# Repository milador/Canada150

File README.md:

# canada150
A PCB to celebrate Canada's 150th birthday

Part List:

    Coin Cell Battery Holder - 20mm x 1 https://www.sparkfun.com/products/783

    Mini Speaker - PC Mount 12mm 2.048kHz x 1 https://www.sparkfun.com/products/7950

    AVR 8 Pin 20MHz 8K 4A/D - ATtiny85 x 1 https://www.sparkfun.com/products/9378

    SPDT Mini Power Switch x 1 https://www.sparkfun.com/products/102

    LED - Basic Red 5mm x 6 https://www.sparkfun.com/products/9590

    DIP Sockets Solder Tail - 8-Pin x 1 (Optional) https://www.sparkfun.com/products/7937

    Header - 2x3 (Male, 0.1") x 1 https://www.sparkfun.com/products/12807 http://www.digikey.com/product-detail/en/amphenol-fci/67997-206HLF/609-3234-ND/1878491

    100 Ohm 1/4W 5% CF MINI x 4 http://www.digikey.ca/product-detail/en/stackpole-electronics-inc/CFM14JT100R/S100QCT-ND/2617658

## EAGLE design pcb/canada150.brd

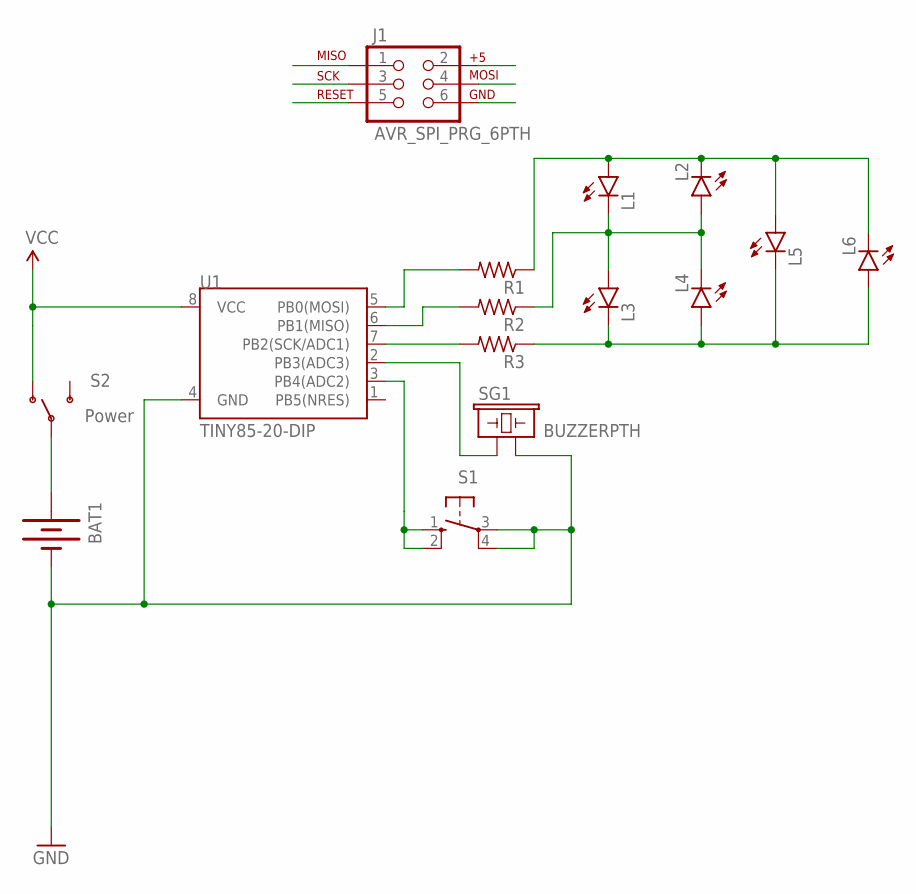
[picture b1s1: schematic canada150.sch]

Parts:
BAT1: BATTERY20PTH; BATTCOM_20MM_PTH
J1: AVR_SPI_PRG_6PTH; 2X3
L1, L2, L3, L4, L5, L6: LED5MM
R1, R2, R3: R-US_0204/7; 0204/7
S1: 10-XX; B3F-10XX
S2: Power; SWITCH-SPDT
SG1: BUZZERPTH; BUZZER-12MM
U1: TINY85-20-DIP; DIP08

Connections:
GND: BAT1.2 (-), J1.6, S1.3, S1.4 (P1), SG1.- (2), U1.4 (GND)
L12: L1.K (C), L2.A, L3.A, L4.K (C), R2.1
MISO: J1.1, R2.2, U1.6 (PB1(MISO))
MOSI: J1.4, R1.2, U1.5 (PB0(MOSI))
unnamed: BAT1.1 (+), S2.2
unnamed: L3.K (C), L4.A, L5.K (C), L6.A, R3.1
unnamed: S1.1 (S), S1.2 (S1), U1.3 (PB4(ADC2))
unnamed: SG1.+ (1), U1.2 (PB3(ADC3))
unnamed: L1.A, L2.K (C), L5.A, L6.K (C), R1.1
RST: J1.5
SCK: J1.3, R3.2, U1.7 (PB2(SCK/ADC1))
VCC: J1.2, S2.1 (O), U1.8 (VCC)

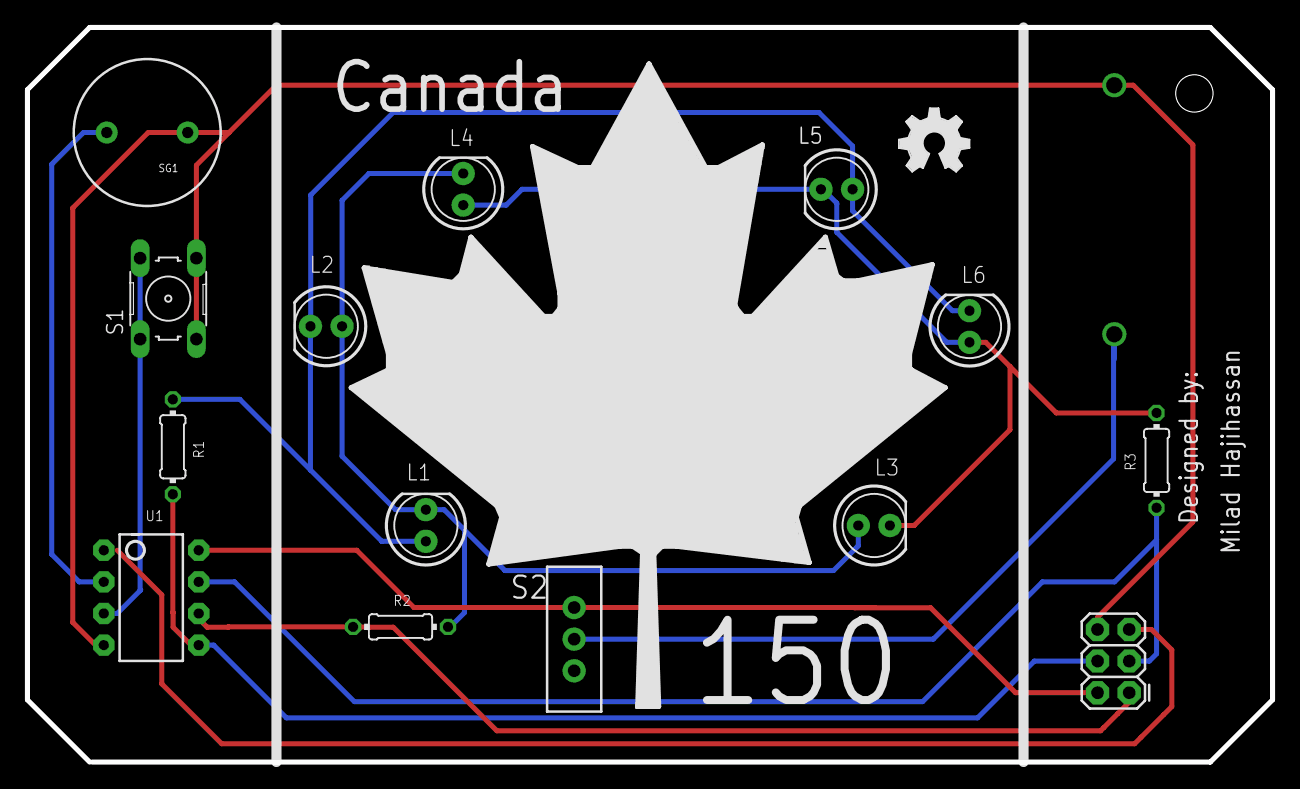
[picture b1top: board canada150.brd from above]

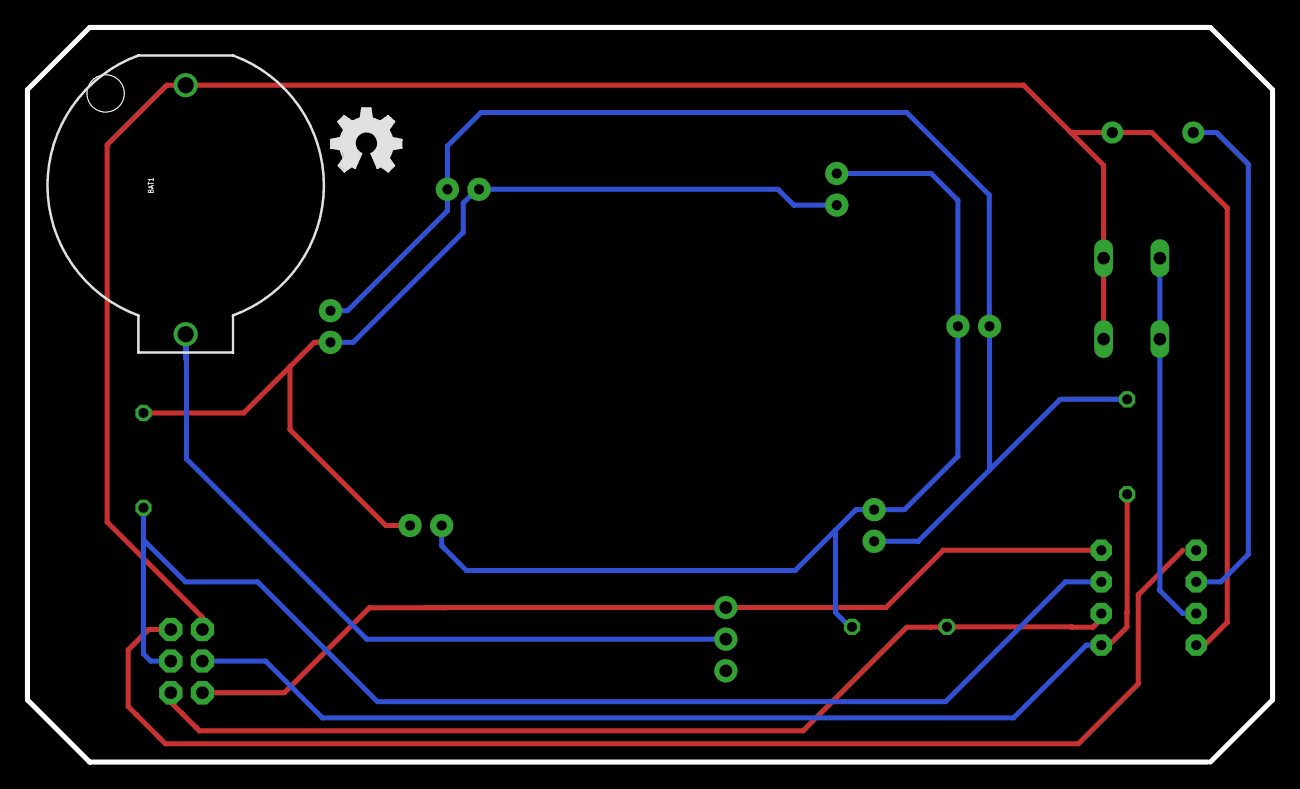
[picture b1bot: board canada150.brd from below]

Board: 2 copper layers, 100.0 x 59.0 mm, 17 parts (2 on the bottom side), 11 nets.

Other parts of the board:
U$1, U$2: OSHW_FILLX200_NOTEXT

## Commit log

2017-08-16 no message
2017-08-17 part list

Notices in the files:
parts and their libraries:
SparkFun: Licensing: CC v3.0 Share-Alike You are welcome to use this library for commercial purposes.
SparkFun-Electromechanical: Licensing: Creative Commons ShareAlike 4.0 International - https://creativecommons.org/licenses/by-sa/4.0
